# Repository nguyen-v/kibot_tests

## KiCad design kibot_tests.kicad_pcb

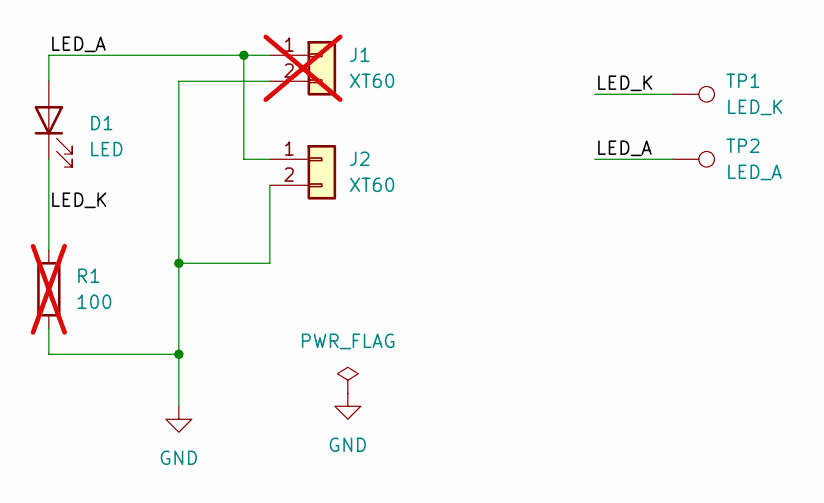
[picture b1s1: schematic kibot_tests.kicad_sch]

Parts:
D1: LED; LED_D1.8mm_W1.8mm_H2.4mm_Horizontal_O6.35mm_Z8.2mm
J1: XT60; AMASS_XT60PW-F_1x02_P7.20mm_Horizontal; not fitted
J2: XT60; AMASS_XT60PW-M_1x02_P7.20mm_Horizontal
R1: 100; C_0603_1608Metric; not fitted
TP1: LED_K; TestPoint_Pad_D0.5mm
TP2: LED_A; TestPoint_Pad_D0.5mm

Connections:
/LED_A: D1.2 (A), J1.1, J2.1, TP2.1
/LED_K: D1.1 (K), R1.1, TP1.1
GND: J1.2, J2.2, R1.2

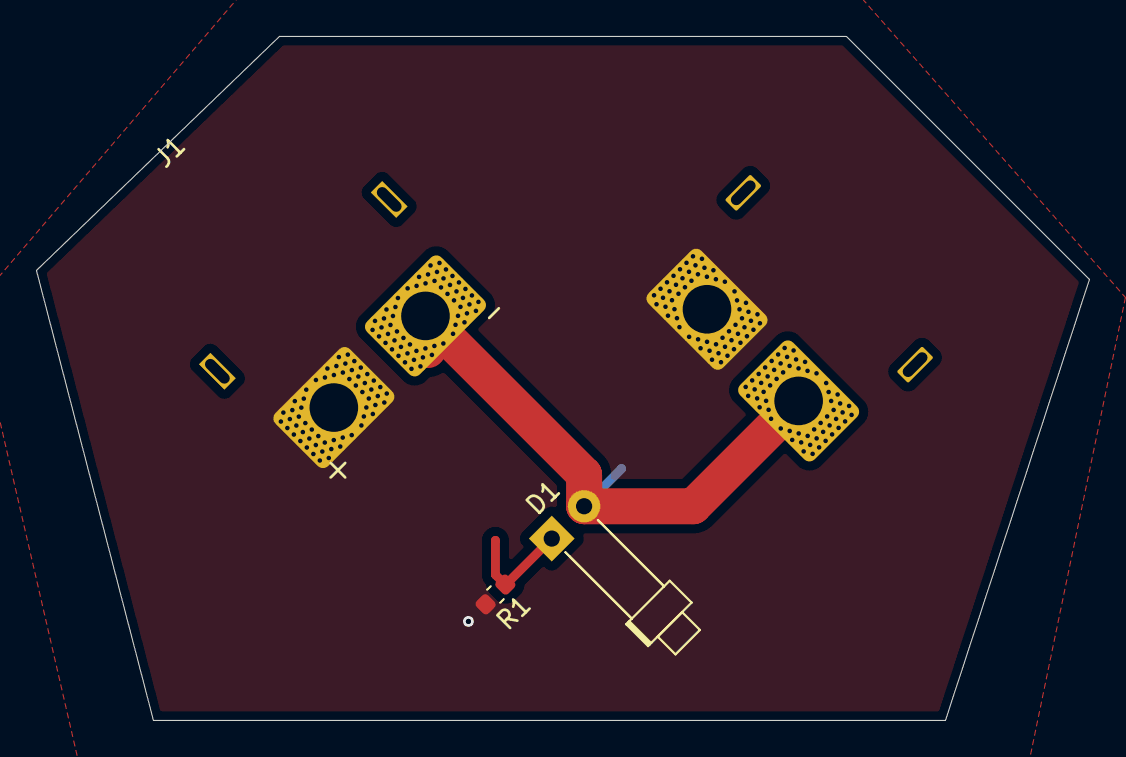
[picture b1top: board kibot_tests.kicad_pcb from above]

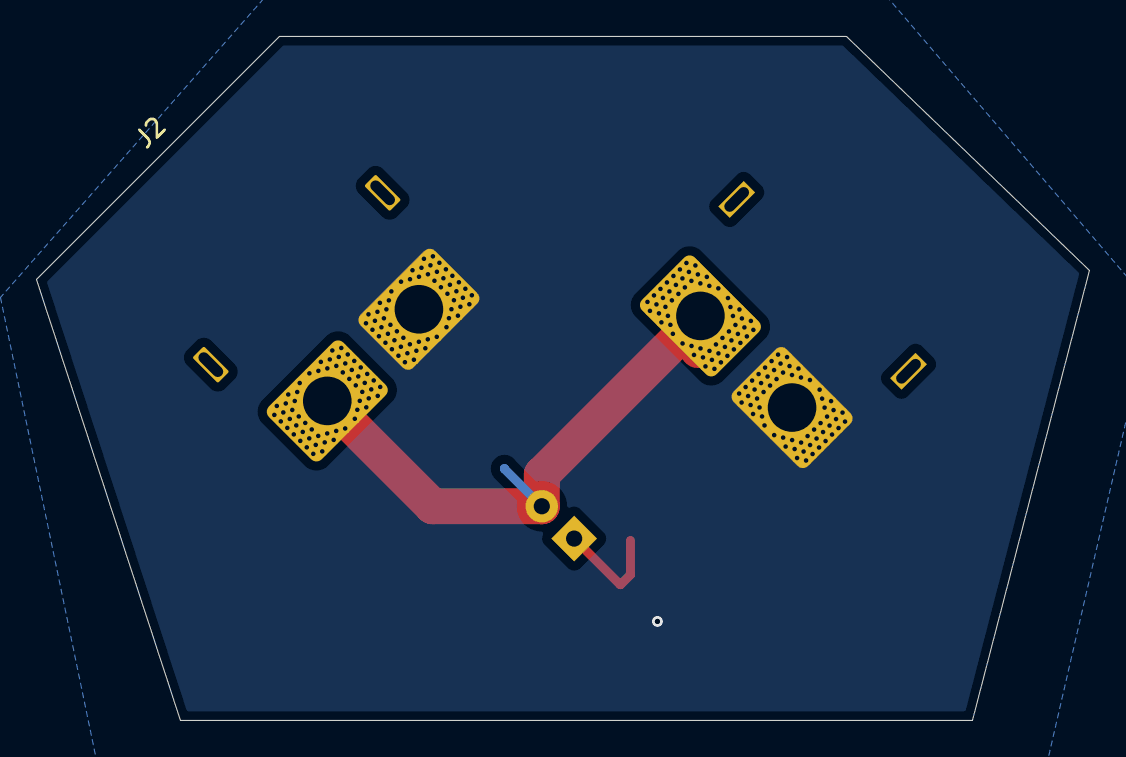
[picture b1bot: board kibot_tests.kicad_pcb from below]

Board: 2 copper layers, 58.5 x 38.0 mm, 6 parts (2 on the bottom side), 3 nets.
